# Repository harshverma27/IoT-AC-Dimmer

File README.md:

# IoT AC Dimmer

ESP32-based wireless phase-angle AC dimmer. Two PCBs linked over ESP-NOW:
a mains-side dimmer board that switches a TRIAC, and a battery-powered
remote with three buttons. Source spec: `IoT AC Dimmer Project.docx`
(v2.0, March 2026).

## What's in this repo

- **Dimmer board** (`hardware/dimmer/`) — 230V mains input, zero-cross
  detection, phase-angle TRIAC control (up to ~2000W / 12A), ESP32 DevKit V1
  running ESP-NOW RX + WiFi.
- **Remote board** (`hardware/remote/`) — LiPo-powered, 3 tactile buttons
  (UP / DOWN / ON-OFF), ESP32 DevKit V1 in deep sleep, ESP-NOW TX only.
- **Generator scripts** (`hardware/tools/`) — Python scripts (on top of
  `kiutils`) that bootstrapped the schematic captures for both boards, so
  the design is reproducible and diffable.

Both boards are designed in KiCad 10. Schematics for both boards are
captured and validated against a `kicad-cli`-exported netlist. PCB layout
is in progress (remote board has a first-pass placement + routing; dimmer
board layout is next).

## Repo layout

```
hardware/
  dimmer/     KiCad project — mains dimmer board (schematic + PCB)
  remote/     KiCad project — battery remote board (schematic + PCB)
  tools/      Python scripts that generated the schematic captures
IoT AC Dimmer Project.docx   Design spec (source of truth for requirements)
CLAUDE.md                    Detailed design notes, GPIO maps, part list
```

See `hardware/README.md`, `hardware/tools/README.md`, and `CLAUDE.md` for
full detail — part lists, GPIO pin maps, and design rationale.

## ⚠️ Safety notice

The dimmer board connects directly to 230V AC mains. It uses an opto-isolated
zero-cross detector (TLP281-4) and an opto-isolated TRIAC driver (MOC3021)
to keep mains-side and logic-side circuitry galvanically isolated, with a
routed FR4 isolation slot under both optoisolators. Do not bridge that
isolation slot with copper or traces, and do not power the dimmer board from
mains and USB at the same time. If you build this, treat it as a mains-voltage
project: use proper enclosures, creepage/clearance spacing, and fusing, and
follow your local electrical code. Build and use at your own risk.

## Hardware overview

### Dimmer board

| Block | Part | Notes |
|-------|------|-------|
| MCU | ESP32 DevKit V1 (30-pin plug-in module) | Core 0: phase timing ISR. Core 1: WiFi/ESP-NOW/MQTT |
| PSU | HLK-PM03 | Isolated 230V→3.3V/900mA, feeds DevKit 3V3 directly (no LDO) |
| AC in/out | MKDSN 5.08mm screw terminals | Live + Neutral |
| Zero-cross detect | TLP281-4 opto + 1N4007 + resistors | 3.3V pulses into GPIO34 |
| Gate drive | MOC3021 opto + resistor | Drives TRIAC gate from GPIO25 |
| Power switch | BT138-600 TRIAC + gate resistor + RC snubber | ~2000W max (12A) |
| Programming | Onboard CP2102 + micro-USB on the DevKit itself | No separate USB circuitry on the carrier board |

### Remote board

| Block | Part | Notes |
|-------|------|-------|
| Battery | LiPo 500mAh 3.7V, JST-PH | Rechargeable |
| Charger | TP4056 charge/protect module (USB-C) | Handles charging, protection, and status LEDs |
| LDO | ME6211 3.3V SOT-23-5 | Regulates battery voltage down to clean 3.3V |
| MCU | ESP32 DevKit V1 (30-pin plug-in module) | ext1 button wakeup, ESP-NOW TX, deep sleep between presses |
| Buttons | 3× 6×6mm tactile THT, pull-up + debounce RC | UP / DOWN / ON-OFF |

Full GPIO maps, exact part numbers, and design rationale (including the
plug-in-DevKit battery-life tradeoff on the remote) live in `CLAUDE.md`.

## Getting started

Requires KiCad 10.

```bash
kicad hardware/dimmer/dimmer.kicad_pro
kicad hardware/remote/remote.kicad_pro
```

The `.kicad_sch` files are KiCad-7 format; KiCad 10 opens and upgrades them
automatically. Don't hand-edit the format version token — see
`hardware/tools/README.md` for why.

To regenerate a schematic capture from the Python generators:

```bash
cd hardware/tools
pip install kiutils
python3 gen_dimmer.py
python3 gen_remote.py
python3 validate.py ../dimmer/dimmer.kicad_sch ../remote/remote.kicad_sch
```

## Status

- Schematics: captured and validated for both boards.
- PCB layout: remote board has first-pass placement/routing; dimmer board
  layout not yet started.
- Firmware: not yet in this repo.

## Firmware plan (not yet implemented)

- Dimmer: hardware timer ISR on Core 0 sets TRIAC fire delay after each
  zero crossing (phase-angle dimming). Networking (WiFi/ESP-NOW/MQTT)
  stays on Core 1.
- Remote: wake on button press (`ext1`), send an ESP-NOW packet, go back
  to deep sleep.
- Future: MQTT + OTA on the dimmer; BLE + display on the remote.

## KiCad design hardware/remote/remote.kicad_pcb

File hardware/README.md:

# Hardware

Two KiCad 10 boards. See root `CLAUDE.md` for the full design spec.

| Dir | Board | Notes |
|-----|-------|-------|
| `dimmer/` | Mains-side AC dimmer | 230V, TRIAC phase control, ESP-NOW RX + WiFi. **Isolation slot required.** |
| `remote/` | Battery remote | LiPo, 3 buttons, ESP-NOW TX, deep sleep |

Each dir holds `*.kicad_pro` / `*.kicad_sch` / `*.kicad_pcb`.

## Status
- **Schematics: captured** for both boards (`dimmer.kicad_sch`, `remote.kicad_sch`).
  Validated by `kicad-cli` netlist export — every functional net matches intent.
- **PCB layout: not started** (`*.kicad_pcb` still blank) — next phase.

The capture was bootstrapped by the scripts in `tools/` (see `tools/README.md`);
the `.kicad_sch` files are the source of truth.

| Board | Parts placed | Key nets |
|-------|-------------|----------|
| dimmer | 31 | mains L/N/L_OUT, ZC detect → GPIO34, gate drive → GPIO25, +3V3/+5V, USB/UART, auto-reset |
| remote | 34 | VBUS/VBAT/+3V3 power path, BTN_UP/DOWN/ONOFF (GPIO39/34/35), USB/UART, auto-reset |

## Workflow
- Open a board: `kicad hardware/dimmer/dimmer.kicad_pro`
  (schematics are KiCad-7 format `20230121`; KiCad 9/10 opens and upgrades them).
- Next: assign/refine footprints, then lay out the PCB — remember the **isolation
  slot** under U2/U3 on the dimmer.
- Analysis / review / BOM / fab: use the **kicad-happy** skills (kicad, bom, jlcpcb, emc…).

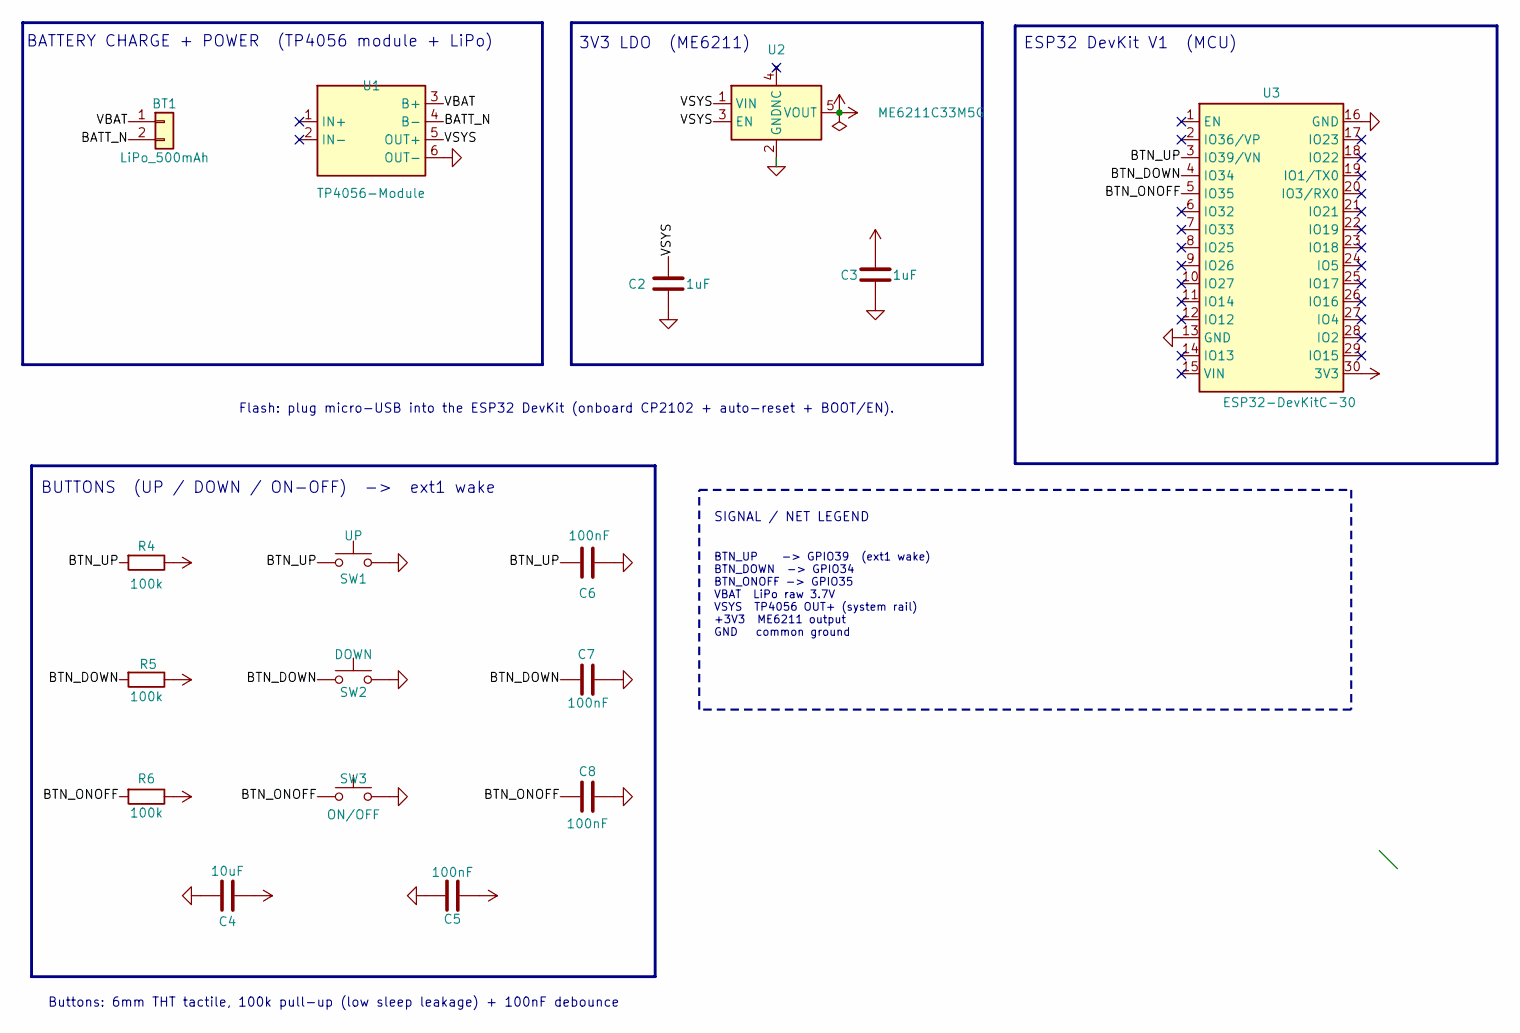
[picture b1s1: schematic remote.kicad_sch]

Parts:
BT1: LiPo_500mAh; JST_PH_S2B-PH-SM4-TB_1x02-1MP_P2.00mm_Horizontal
C2, C3: 1uF; C_0805_2012Metric
C4: 10uF; C_1206_3216Metric
C5, C6, C7, C8: 100nF; C_0805_2012Metric
R4, R5, R6: 100k; R_0805_2012Metric
SW1: UP; SW_PUSH_6mm
SW2: DOWN; SW_PUSH_6mm
SW3: ON/OFF; SW_PUSH_6mm
U1: TP4056-Module; PinHeader_1x06_P2.54mm_Vertical
U2: ME6211C33M5G; SOT-23-5
U3: ESP32-DevKitC-30

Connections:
+3V3: C3.1, C4.1, C5.1, R4.1, R5.1, R6.1, U2.5 (VOUT), U3.30 (3V3)
/BATT_N: BT1.2, U1.4 (B-)
/BTN_DOWN: C7.1, R5.2, SW2.1, U3.4 (IO34)
/BTN_ONOFF: C8.1, R6.2, SW3.1, U3.5 (IO35)
/BTN_UP: C6.1, R4.2, SW1.1, U3.3 (IO39/VN)
/VBAT: BT1.1, U1.3 (B+)
/VSYS: C2.1, U1.5 (OUT+), U2.1 (VIN), U2.3 (EN)
GND: C2.2, C3.2, C4.2, C5.2, C6.2, C7.2, C8.2, SW1.2, SW2.2, SW3.2, U1.6 (OUT-), U2.2 (GND), U3.13 (GND), U3.16 (GND)

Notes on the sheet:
Flash: plug micro-USB into the ESP32 DevKit (onboard CP2102 + auto-reset + BOOT/EN).
BATTERY CHARGE + POWER (TP4056 module + LiPo)
3V3 LDO (ME6211)
SIGNAL / NET LEGEND
BTN_UP -> GPIO39 (ext1 wake) BTN_DOWN -> GPIO34 BTN_ONOFF -> GPIO35 VBAT LiPo raw 3.7V VSYS TP4056 OUT+ (system rail) +3V3 ME6211 output GND common ground
Buttons: 6mm THT tactile, 100k pull-up (low sleep leakage) + 100nF debounce
BUTTONS (UP / DOWN / ON-OFF) -> ext1 wake
ESP32 DevKit V1 (MCU)

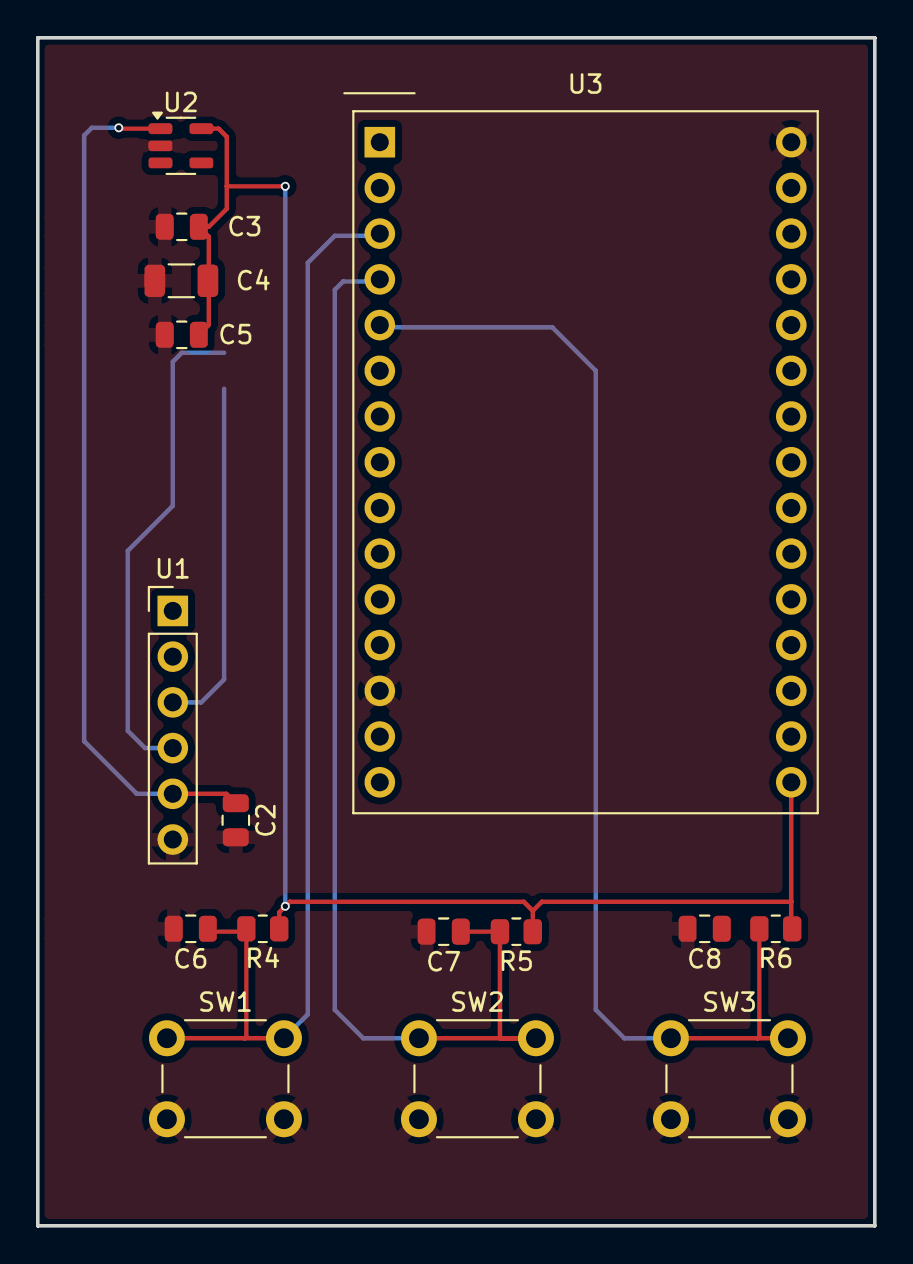
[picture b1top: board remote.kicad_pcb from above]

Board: 2 copper layers, 46.5 x 66.0 mm, 17 parts (1 on the bottom side), 8 nets.
